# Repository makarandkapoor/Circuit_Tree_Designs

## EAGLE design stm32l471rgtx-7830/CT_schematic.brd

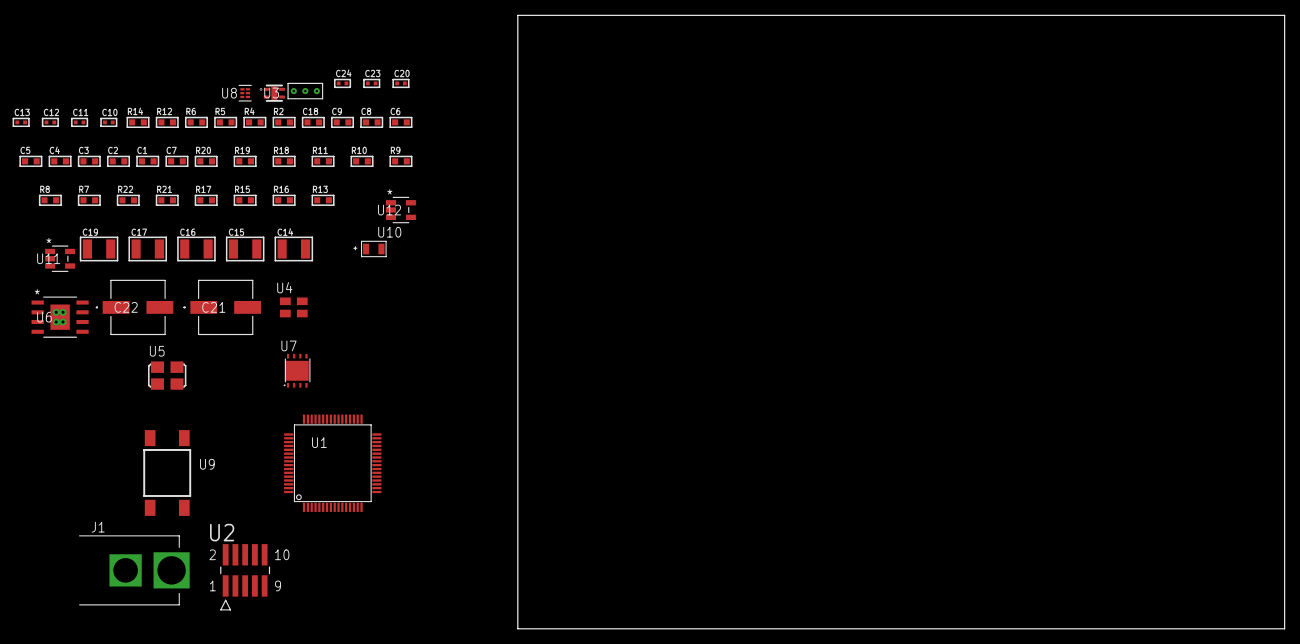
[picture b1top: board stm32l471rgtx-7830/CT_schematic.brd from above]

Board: 2 copper layers, 100.0 x 80.0 mm, 58 parts (0 on the bottom side), 26 nets, no tracks yet.

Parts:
C1, C9, C18: 1e-06; C0603
C2, C3, C4, C5, C6: 1e-07; C0603
C7: 4.7e-06; C0603
C8: 1e-08; C0603
C10, C11, C20: 1e-07; C0402
C12, C13, C23, C24: 1e-08; C0402
C14, C15, C16, C17, C19: 1e-05; C1210
C21, C22: 0.0001; EXV-9H
J1: PJ-037B; PJ-037B_PACKAGE
R2: 1000.0; R0603
R4: 4700.0; R0603
R5, R6, R14: 2200.0; R0603
R7, R8, R9, R10, R11, R18, R19: 10000.0; R0603
R12: 5.0; R0603
R13: 1402.2764227642; R0603
R15, R17: 100000.0; R0603
R16: 153694.38; R0603
R20: 82000.0; R0603
R21: 300000.0; R0603
R22: 120000.0; R0603
U1: STM32L471RGT6; LQFP64
U2: FTSH-105-01-L-DV-K; SAMTEC_FTSH-105-01-L-DV-K
U3: Si7034-A10-IM; SI7034-A10-IM
U4: ASEK-32.768KHz-ECST; ASEK
U5: ASFL1-25MHZ-NCS; ASFL1
U6: MIC5234YME; SOIC-8_EP
U7: LP2951ACSDX/NOPB; WSON-8
U8: TPS3895ADRYR; SON-6
U9: 4-1437565-2; SW_4-1437565-2
U10: Q65110A2395; LGM67K-G1J2-24-Z
U11, U12: nc7sz125m5x; NC7SZ125M5X
U13: Dummy; DUMMY_PACKAGE_127

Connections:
CLK_U1_3: U1.3, U4.3
CLK_U1_5: U1.5, U5.3
GND: C1.2, C2.2, C3.2, C4.2, C5.2, C6.2, C7.2, C8.2, C9.2, C10.2, C11.2, C12.2, C13.2, C14.2, C15.2, C16.2, C17.2, C18.2, C19.2, C20.2, C21.2, C22.2, C23.2, C24.2, J1.2, R2.2, R7.2, R11.2, R12.2, R14.2, R17.2, R20.2, R22.2, U1.12, U1.18, U1.31, U1.47, U1.63, U2.3, U2.5, U3.5, U4.2, U5.2, U6.7, U6.EPAD, U7.3, U7.4, U7.PAD, U8.2, U10.C, U11.2, U11.3, U12.1, U12.3, U13.1
NET_U1_7: R4.1, U1.7, U12.4
NET_U1_58: R5.1, U1.58, U3.2
NET_U1_59: R6.1, U1.59, U3.4
NET_U1_60: R7.1, U1.60
NET_U1_62: U9.3, U9.4
NET_U2_4: R11.1, U2.4
NET_U2_9: R12.1, U2.9
NET_U6_4: R13.2, R14.1, U6.4
NET_U7_5: R15.1, U7.5
NET_U7_7: R16.2, R17.1, U7.7
NET_U8_1: R19.1, R20.1, U8.1
NET_U8_3: R21.2, R22.1, U8.3
NET_U8_4: R18.1, U8.4, U11.4, U12.2
NET_U9_1: R2.1, U9.1, U9.2
PROC_SYS_JTDI: R9.1, U1.50, U2.8
PROC_SYS_JTDO_SWO: U1.55, U2.6
PROC_SYS_JTMS_SWDIO: R10.1, U1.46, U2.2
PROC_TIM1_CH2: U1.42, U13.2
PROC_TIM1_CH4: U1.44, U13.3
RST_OUT_U2_JTAG_RST_B: R8.1, U2.10, U11.1
VCC_S1_5V5: C14.1, C15.1, C18.1, C21.1, C22.1, J1.1, U6.5, U6.8, U7.8
VCC_TIER1_1V8: C1.1, C2.1, C3.1, C4.1, C5.1, C6.1, C7.1, C8.1, C9.1, C10.1, C11.1, C16.1, C17.1, C20.1, C23.1, C24.1, R4.2, R5.2, R6.2, R8.2, R9.2, R10.2, R13.1, R18.2, R19.2, R21.1, U1.1, U1.13, U1.19, U1.32, U1.48, U1.64, U2.1, U3.1, U6.1, U8.6, U11.5, U12.5
VCC_TIER1_3V3: C12.1, C13.1, C19.1, R15.2, R16.1, U4.4, U5.4, U7.1

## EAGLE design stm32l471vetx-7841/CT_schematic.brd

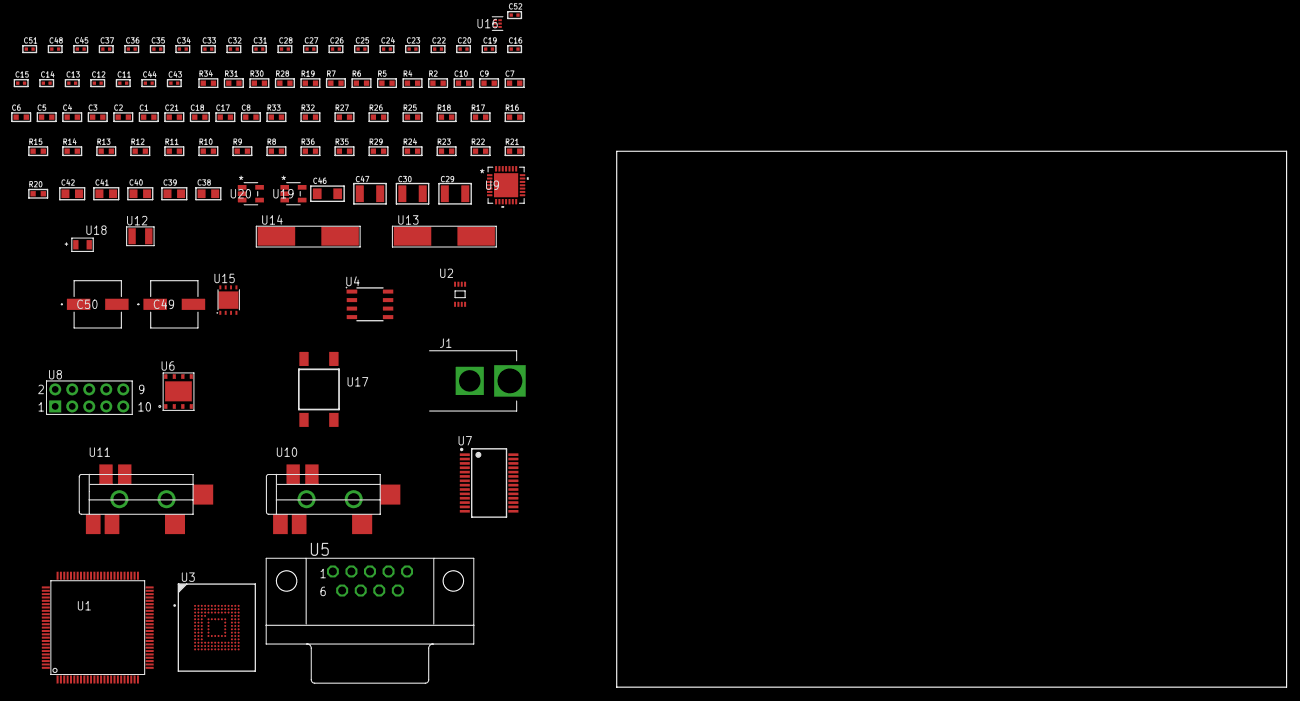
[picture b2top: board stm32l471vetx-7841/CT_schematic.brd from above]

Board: 2 copper layers, 100.0 x 80.0 mm, 107 parts (0 on the bottom side), 67 nets, no tracks yet.

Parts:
C1, C10: 1e-06; C0603
C2, C3, C4, C5, C6, C7: 1e-07; C0603
C8: 4.7e-06; C0603
C9: 1e-08; C0603
C11, C12, C13, C14: 1e-11; C0402
C15, C45, C51, C52: 1e-08; C0402
C16, C19, C20, C22, C23, C24, C25, C26, C27, C28, C33, C34, C35, C36, C37, C48: 1e-07; C0402
C17, C18, C21: 2.2e-06; C0603
C29, C30: 2.2e-05; C1210
C31, C32: 1e-09; C0402
C38, C39, C40, C41, C42: 1e-05; C0805
C43, C44: 2.2e-11; C0402
C46: 1e-05; C1206
C47: 1e-05; C1210
C49, C50: 0.0001; EXV-9H
J1: PJ-037B; PJ-037B_PACKAGE
R2, R31: 1000.0; R0603
R4, R5: 4700.0; R0603
R6, R7: 2200.0; R0603
R8, R32, R33: 10000.0; R0603
R9, R10, R11, R12, R13, R14, R15, R16, R17, R18: 34000.0; R0603
R19: 120.0; R0603
R20, R21, R22, R23, R24, R29: 100000.0; R0603
R25, R26, R27: 47000.0; R0603
R28: 680.0; R0603
R30: 2231.0; R0603
R34: 9100.0; R0603
R35: 680000.0; R0603
R36: 120000.0; R0603
U1: STM32L471VET6; LQFP100
U2: 24AA00T-I/MNY; TDFN-8/6MM
U3: mtfc4gmcdm; TFBGA-153
U4: SN65HVD230D; SOIC-8
U5: 182-009-113R531; 182-009-MALE
U6: SST26VF032B-104I/MF; WFDN-8
U7: ST3241EBPR; SSOP-28
U8: HTSS-105-01-G-D
U9: WM8731CLSEFL; QFN-28
U10, U11: SJ-43515TS-SMT-TR
U12: ABS07-32.768KHZ-7-T
U13: ABLS-25.000MHZ-B2F-T
U14: ABLS-12.288MHZ-B4-T
U15: LP3878SDX-ADJ/NOPB; WSON-8
U16: TPS3895ADRYR; SON-6
U17: 4-1437565-2; SW_4-1437565-2
U18: Q65110A2395; LGM67K-G1J2-24-Z
U19, U20: nc7sz125m5x; NC7SZ125M5X

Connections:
CLK_CRYSTAL_U1_8: C11.1, U1.8, U12.1
CLK_CRYSTAL_U1_9: C12.1, U1.9, U12.2
CLK_CRYSTAL_U1_12: C13.1, U1.12, U13.1
CLK_CRYSTAL_U1_13: C14.1, U1.13, U13.2
CLK_CRYSTAL_U9_1: C43.1, U9.1, U14.1
CLK_CRYSTAL_U9_2: C44.1, U9.2, U14.2
GND: C1.2, C2.2, C3.2, C4.2, C5.2, C6.2, C7.2, C8.2, C9.2, C10.2, C11.2, C12.2, C13.2, C14.2, C15.2, C16.2, C17.2, C18.2, C19.2, C20.2, C21.2, C22.2, C23.2, C24.2, C27.2, C28.2, C32.2, C33.2, C34.2, C35.2, C36.2, C37.2, C38.2, C39.2, C40.2, C41.2, C42.2, C43.2, C44.2, C45.2, C46.2, C47.2, C48.2, C49.2, C50.2, C51.2, C52.2, J1.2, R2.2, R8.2, R20.2, R25.2, R26.2, R27.2, R31.2, R34.2, R36.2, U1.10, U1.19, U1.20, U1.27, U1.49, U1.74, U1.99, U2.4, U3.C4, U3.E7, U3.G5, U3.H10, U3.K8, U3.N2, U3.N5, U3.P4, U3.P6, U4.2, U5.5, U6.4, U6.9, U7.23, U7.25, U8.9, U9.4, U9.15, U9.19, U9.25, U9.26, U9.29, U10.1, U11.1, U15.3, U15.PAD, U16.2, U18.C, U19.1, U19.3, U20.1, U20.3
NET_U1_14: R5.1, U1.14, U20.4
NET_U1_92: R6.1, U1.92, U2.6
NET_U1_93: R7.1, U1.93, U2.5
NET_U1_94: R8.1, U1.94
NET_U1_98: U17.3, U17.4
NET_U3_C2: C18.1, C19.1, U3.C2
NET_U3_K5: R4.1, U3.K5, U19.4
NET_U4_6: R19.2, U4.6
NET_U4_8: R20.1, U4.8
NET_U5_2: R19.2, U4.6, U5.2
NET_U5_3: R19.1, U4.7, U5.3
NET_U7_1: C26.1, U7.1
NET_U7_2: C26.2, U7.2
NET_U7_3: C28.1, U7.3
NET_U7_22: R24.1, U7.22
NET_U7_24: C25.2, U7.24
NET_U7_27: C27.1, U7.27
NET_U7_28: C25.1, U7.28
NET_U8_3: U7.4, U8.3
NET_U8_4: U7.5, U8.4
NET_U8_5: U7.9, U8.5
NET_U8_6: U7.10, U8.6
NET_U9_20: C37.1, C42.1, U9.20
NET_U10_2: C30.1, R26.1, U10.2
NET_U10_5: C29.1, R25.1, U10.5
NET_U11_5: C31.1, C32.1, R27.1, R28.1, U11.5
NET_U15_1: C45.1, U15.1
NET_U15_6: R30.2, R31.1, U15.6
NET_U15_8: R29.1, U15.8
NET_U16_1: R33.1, R34.1, U16.1
NET_U16_3: R35.2, R36.1, U16.3
NET_U16_4: R32.1, U16.4, U19.2, U20.2
NET_U17_1: R2.1, U17.1, U17.2
PROC_CAN1_RX: U1.70, U4.4
PROC_CAN1_TX: U1.71, U4.1
PROC_LPUART1_CTS: U1.52, U7.13
PROC_LPUART1_RTS: U1.51, U7.18
PROC_LPUART1_RX: U1.15, U7.19
PROC_LPUART1_TX: U1.16, U7.14
PROC_QUADSPI_BK1_IO0: U1.36, U6.5
PROC_QUADSPI_BK1_IO1: U1.35, U6.2
PROC_QUADSPI_BK1_IO2: R22.1, U1.32, U6.3
PROC_QUADSPI_BK1_IO3: R23.1, U1.31, U6.7
PROC_QUADSPI_CLK: U1.41, U6.6
PROC_QUADSPI_NCS: R21.1, U1.42, U6.1
PROC_SAI1_FS_A: U1.3, U9.9, U9.11
PROC_SAI1_SCK_A: U1.4, U9.7
PROC_SAI1_SD_A: U1.5, U9.8
PROC_SDMMC1_CK: R18.1, U1.80, U3.M6
PROC_SDMMC1_CMD: R17.1, U1.83, U3.M5
PROC_SDMMC1_D0: R9.1, U1.65, U3.A3
PROC_SDMMC1_D1: R10.1, U1.66, U3.A4
PROC_SDMMC1_D2: R11.1, U1.78, U3.A5
PROC_SDMMC1_D3: R12.1, U1.79, U3.B2
PROC_SDMMC1_D4: R13.1, U1.95, U3.B3
PROC_SDMMC1_D5: R14.1, U1.96, U3.B4
PROC_SDMMC1_D6: R15.1, U1.63, U3.B5
PROC_SDMMC1_D7: R16.1, U1.64, U3.B6
VCC_S1_9V4: C46.1, C49.1, C50.1, J1.1, R29.2, U15.4
VCC_TIER1_3V3: C1.1, C2.1, C3.1, C4.1, C5.1, C6.1, C7.1, C8.1, C9.1, C10.1, C15.1, C16.1, C17.1, C20.1, C21.1, C22.1, C23.1, C24.1, C33.1, C34.1, C35.1, C36.1, C38.1, C39.1, C40.1, C41.1, C47.1, C48.1, C51.1, C52.1, R4.2, R5.2, R6.2, R7.2, R9.2, R10.2, R11.2, R12.2, R13.2, R14.2, R15.2, R16.2, R17.2, R18.2, R21.2, R22.2, R23.2, R24.2, R30.1, R32.2, R33.2, R35.1, U1.6, U1.11, U1.21, U1.22, U1.28, U1.50, U1.73, U1.75, U1.100, U2.8, U3.C6, U3.E6, U3.F5, U3.J10, U3.K9, U3.M4, U3.N4, U3.P3, U3.P5, U4.3, U6.8, U7.26, U9.3, U9.5, U9.12, U9.18, U15.5, U16.6, U19.5, U20.5

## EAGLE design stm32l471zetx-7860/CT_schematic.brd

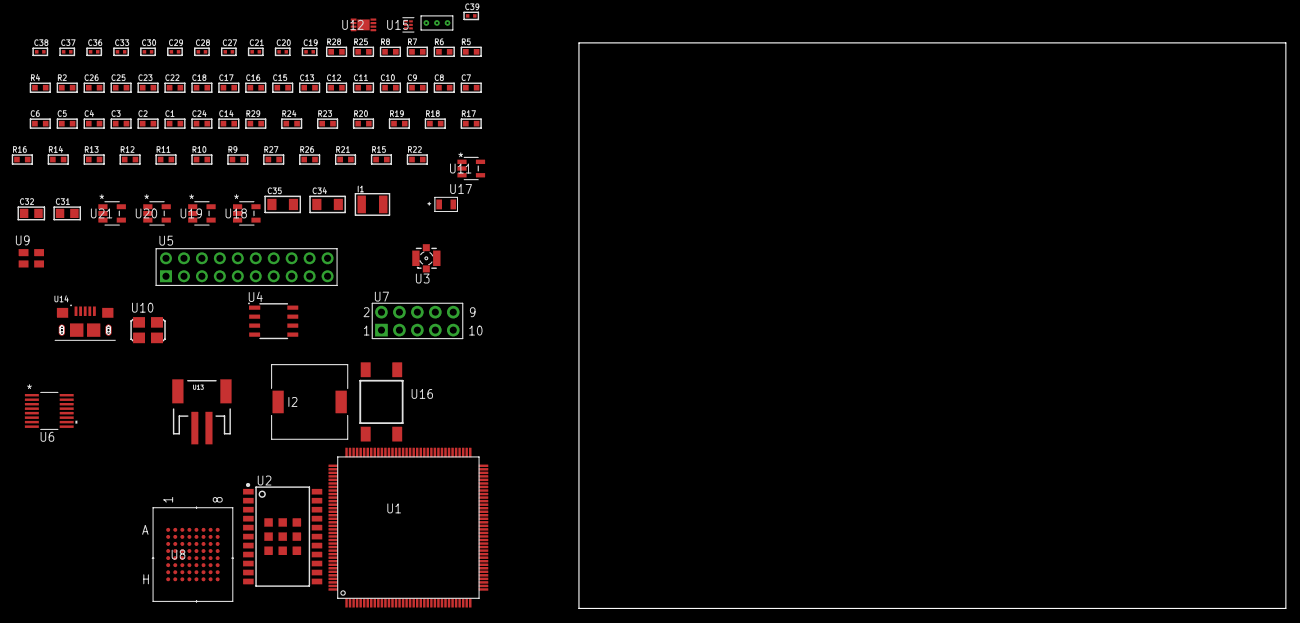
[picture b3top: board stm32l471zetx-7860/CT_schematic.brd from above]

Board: 2 copper layers, 173.4 x 80.0 mm, 90 parts (0 on the bottom side), 97 nets, no tracks yet.

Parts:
C1, C18, C22, C23, C25, C26: 1e-06; C0603
C2, C3, C4, C5, C6, C7, C8, C9, C10, C11, C12, C13, C15, C16: 1e-07; C0603
C14: 4.7e-06; C0603
C17: 1e-08; C0603
C19, C21, C33: 1e-07; C0402
C20, C27, C28, C29, C30, C36, C37, C38, C39: 1e-08; C0402
C24: 2.2e-07; C0603
C31, C32: 1e-05; C0805
C34, C35: 1e-05; C1206
I1: 1e-05; L1210
I2: 2.5e-06; DR1040
R2: 1000.0; R0603
R4, R5, R6: 4700.0; R0603
R7, R8: 2200.0; R0603
R9, R10, R11, R12, R13, R14, R16, R17, R18, R19, R20, R23, R24, R29: 10000.0; R0603
R15: 100000.0; R0603
R21: 220000.0; R0603
R22: 1000000.0; R0603
R25: 9100.0; R0603
R26: 680000.0; R0603
R27: 120000.0; R0603
R28: 2000.0; R0603
U1: STM32L471ZET6; LQFP144
U2: A2200-A
U3: 73412-0114; COAXIAL_C
U4: AT25040B-SSHL-T; SOIC-8
U5: TST-110-05-T-D-RA
U6: LTC2804CGN-1#PBF; SSOP-16
U7: HTSS-105-01-G-D
U8: mt28ew256aba1HPC-0SIT; LBGA-64
U9: ASEK-32.768KHz-ECST; ASEK
U10: ASFL1-25MHZ-NCS; ASFL1
U11: ltc3406es5; TSOT-23-5
U12: MCP73831T-2ACI/MC; DFN8_2X3MC
U13: S2B-PH-SM4-TB(LF)(SN); JST-2-SMD
U14: 10118193-0001LF; FCI_10118193-0001LF
U15: TPS3895ADRYR; SON-6
U16: 4-1437565-2; SW_4-1437565-2
U17: Q65110A2395; LGM67K-G1J2-24-Z
U18, U19, U20, U21: nc7sz125m5x; NC7SZ125M5X
U22: Dummy; DUMMY_PACKAGE_204

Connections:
CLK_U1_8: U1.8, U9.3
CLK_U1_23: U1.23, U10.3
GND: C1.2, C2.2, C3.2, C4.2, C5.2, C6.2, C7.2, C8.2, C9.2, C10.2, C11.2, C12.2, C13.2, C14.2, C15.2, C16.2, C17.2, C18.2, C19.2, C20.2, C21.2, C22.2, C23.2, C25.2, C26.2, C27.2, C28.2, C29.2, C30.2, C31.2, C32.1, C32.2, C33.2, C34.2, C35.2, C36.2, C37.2, C38.2, C39.2, R2.2, R9.2, R21.2, R25.2, R27.2, R28.2, U1.16, U1.30, U1.31, U1.38, U1.51, U1.61, U1.71, U1.83, U1.94, U1.107, U1.120, U1.130, U1.143, U2.7, U2.8, U2.23, U2.24, U2.25, U2.26, U2.27, U2.28, U2.29, U2.30, U2.31, U4.4, U5.4, U5.6, U5.8, U5.10, U5.12, U5.14, U5.16, U5.18, U5.20, U6.8, U7.9, U8.E8, U8.H2, U8.H7, U9.2, U10.2, U11.2, U12.6, U12.9, U13.2, U14.5, U14.6, U14.7, U14.8, U14.9, U15.2, U17.C, U18.2, U18.3, U19.1, U19.3, U20.1, U20.3, U21.1, U21.3, U22.1
INPUT_USBPOWER_5V: C34.1, R29.2, U12.1, U12.2, U14.1
NET_U1_25: R6.1, U1.25, U21.4
NET_U1_128: R8.1, U1.128, U2.16
NET_U1_129: R7.1, U1.129, U2.15
NET_U1_138: R9.1, U1.138
NET_U1_142: U16.3, U16.4
NET_U2_2: R10.2, U2.2
NET_U2_17: R10.1, U2.17
NET_U2_22: R5.1, U2.22, U20.4
NET_U3_1: U2.11, U3.1
NET_U3_2: U2.10, U3.2, U3.3, U3.4
NET_U4_3: R11.1, U4.3
NET_U4_7: R13.1, U4.7
NET_U6_6: C22.1, U6.6
NET_U6_7: C24.1, I1.2, U6.7
NET_U6_9: C23.1, U6.9
NET_U6_10: C24.2, U6.10
NET_U6_11: R15.1, U6.11
NET_U7_3: U6.1, U7.3
NET_U7_4: U6.2, U7.4
NET_U7_5: U6.3, U7.5
NET_U7_6: U6.4, U7.6
NET_U8_B4: R19.1, U8.B4
NET_U8_B5: R4.1, U8.B5, U19.4
NET_U11_3: I2.1, U11.3
NET_U11_5: R21.1, R22.1, U11.5
NET_U11_ATNET_3: I2.2, R22.2
NET_U12_5: R29.1, U12.5
NET_U12_8: R28.1, U12.8
NET_U15_1: R24.1, R25.1, U15.1
NET_U15_3: R26.2, R27.1, U15.3
NET_U15_4: R23.1, U15.4, U18.4, U19.2, U20.2, U21.2
NET_U16_1: R2.1, U16.1, U16.2
PROC_FMC_A0: U1.10, U8.E2
PROC_FMC_A1: U1.11, U8.D2
PROC_FMC_A2: U1.12, U8.C2
PROC_FMC_A3: U1.13, U8.A2
PROC_FMC_A4: U1.14, U8.B2
PROC_FMC_A5: U1.15, U8.D3
PROC_FMC_A6: U1.50, U8.C3
PROC_FMC_A7: U1.53, U8.A3
PROC_FMC_A8: U1.54, U8.B6
PROC_FMC_A9: U1.55, U8.A6
PROC_FMC_A10: U1.56, U8.C6
PROC_FMC_A11: U1.57, U8.D6
PROC_FMC_A12: U1.87, U8.B7
PROC_FMC_A13: U1.88, U8.A7
PROC_FMC_A14: U1.89, U8.C7
PROC_FMC_A15: U1.90, U8.D7
PROC_FMC_A16: U1.80, U8.E7
PROC_FMC_A17: U1.81, U8.B3
PROC_FMC_A18: U1.82, U8.C4
PROC_FMC_A19: U1.2, U8.D5
PROC_FMC_A20: U1.3, U8.D4
PROC_FMC_A21: U1.4, U8.C5
PROC_FMC_A22: U1.5, U8.B8
PROC_FMC_A23: U1.1, U8.C8
PROC_FMC_D0: U1.85, U8.E3
PROC_FMC_D1: U1.86, U8.H3
PROC_FMC_D2: U1.114, U8.E4
PROC_FMC_D3: U1.115, U8.H4
PROC_FMC_D4: U1.58, U8.H5
PROC_FMC_D5: U1.59, U8.E5
PROC_FMC_D6: U1.60, U8.H6
PROC_FMC_D7: U1.63, U8.E6
PROC_FMC_D8: U1.64, U8.F3
PROC_FMC_D9: U1.65, U8.G3
PROC_FMC_D10: U1.66, U8.F4
PROC_FMC_D11: U1.67, U8.G4
PROC_FMC_D12: U1.68, U8.F5
PROC_FMC_D13: U1.77, U8.G6
PROC_FMC_D14: U1.78, U8.F6
PROC_FMC_D15: U1.79, U8.G7
PROC_FMC_NBL0: R20.1, U1.141, U8.F7
PROC_FMC_NE2: R16.1, U1.124, U8.F2
PROC_FMC_NOE: R17.1, U1.118, U8.G2
PROC_FMC_NWAIT: U1.122, U8.A4
PROC_FMC_NWE: R18.1, U1.119, U8.A5
PROC_LPUART1_CTS: U1.74, U6.13
PROC_LPUART1_RTS: U1.73, U6.15
PROC_LPUART1_RX: U1.26, U6.16
PROC_LPUART1_TX: U1.27, U6.14
PROC_PC13: U1.7, U22.2
PROC_PC15_OSC32_OUT: U1.9, U22.3
PROC_SPI1_MISO: U1.42, U4.2
PROC_SPI1_MOSI: U1.43, U4.5
PROC_SPI1_NSS: R12.1, U1.40, U4.1
PROC_SPI1_SCK: U1.41, U4.6
PROC_SYS_JTCK_SWCLK: U1.109, U5.9
PROC_SYS_JTDO_SWO: U1.133, U5.13
PROC_SYS_JTMS_SWDIO: U1.105, U5.7
RST_OUT_U5_SRESET_B: R14.1, U5.15, U18.1
VCC_S1_3V7: C31.1, C35.1, U11.4, U12.3, U12.4, U13.1
VCC_TIER1_3V3: C1.1, C2.1, C3.1, C4.1, C5.1, C6.1, C7.1, C8.1, C9.1, C10.1, C11.1, C12.1, C13.1, C14.1, C15.1, C16.1, C17.1, C18.1, C19.1, C20.1, C21.1, C25.1, C26.1, C27.1, C28.1, C29.1, C30.1, C32.2, C33.1, C36.1, C37.1, C38.1, C39.1, I1.1, I2.2, R4.2, R5.2, R6.2, R7.2, R8.2, R11.2, R12.2, R13.2, R14.2, R15.2, R16.2, R17.2, R18.2, R19.2, R20.2, R22.2, R23.2, R24.2, R26.1, U1.6, U1.17, U1.32, U1.33, U1.39, U1.52, U1.62, U1.72, U1.84, U1.95, U1.106, U1.108, U1.121, U1.131, U1.144, U2.20, U4.8, U5.1, U6.5, U6.12, U8.D8, U8.F1, U8.G5, U9.4, U10.4, U15.6, U18.5, U19.5, U20.5, U21.5

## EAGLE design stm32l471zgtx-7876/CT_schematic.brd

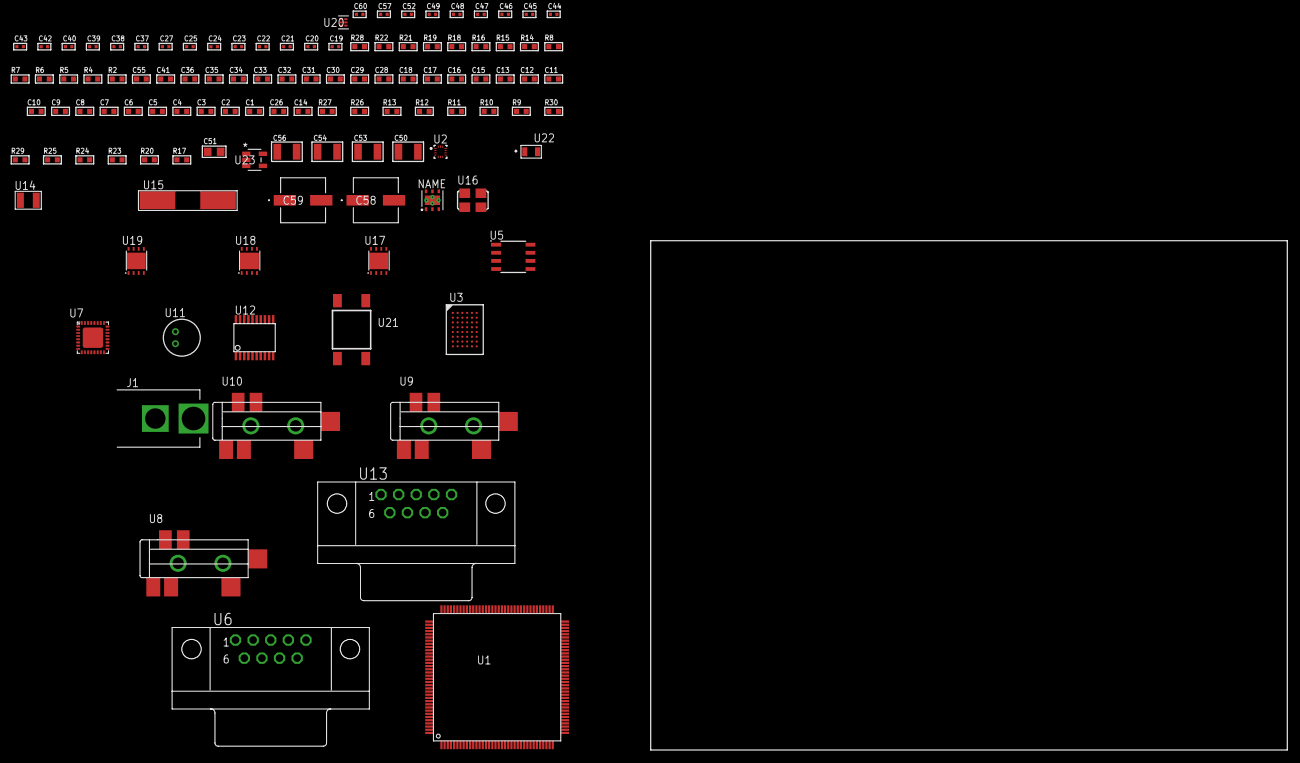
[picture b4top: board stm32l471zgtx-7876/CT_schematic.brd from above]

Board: 2 copper layers, 100.0 x 80.0 mm, 112 parts (0 on the bottom side), 102 nets, no tracks yet.

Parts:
C1, C18, C28, C29, C30, C31, C32, C33, C34, C35, C36, C41: 1e-06; C0603
C2, C3, C4, C5, C6, C7, C8, C9, C10, C11, C12, C13, C15, C16: 1e-07; C0603
C14: 4.7e-06; C0603
C17: 1e-08; C0603
C19, C20, C21, C22: 1e-11; C0402
C23, C24, C25, C37, C38, C39, C40, C42, C43, C44, C45, C46, C47, C57: 1e-07; C0402
C26: 2.2e-06; C0603
C27, C48, C49, C52, C60: 1e-08; C0402
C50, C53, C54, C56: 1e-05; C1210
C51: 1e-05; C0805
C55: 8e-07; R0603
C58, C59: 0.0001; EXV-9H
J1: PJ-037B; PJ-037B_PACKAGE
R2, R19, R22: 1000.0; R0603
R4: 4700.0; R0603
R5, R6, R7, R8: 2200.0; R0603
R9, R10, R11, R12, R13, R26, R27: 10000.0; R0603
R14: 120.0; R0603
R15, R16: 1270.0; R0603
R17, R20, R23, R25: 100000.0; R0603
R18: 200.0; R0603
R21: 2231.0; R0603
R24: 300000.0; R0603
R28: 9100.0; R0603
R29: 680000.0; R0603
R30: 120000.0; R0603
U1: STM32L471ZGT6; LQFP144
U2: BMC150; LGA14R35P5X6_200X200X100
U3: CY62147GE30-45BVXI; VFBGA48
U4: HDC1080DMBR; WSON-6
U5: MCP2562-E/SN; SOIC-8
U6, U13: 182-009-113R531; 182-009-MALE
U7: SGTL5000XNAA3; QFN-32
U8, U9, U10: SJ-43515TS-SMT-TR
U11: WM-64PCT; WM-64PC
U12: SP3203ECY-L/TR; TSSOP20-I
U14: ABS07-32.768KHZ-7-T
U15: ABLS-25.000MHZ-B2F-T
U16: ASFL-24.57MHZ-NCS; ASFL1
U17, U18: LP3878SDX-ADJ/NOPB; WSON-8
U19: LP2951ACSDX/NOPB; WSON-8
U20: TPS3895ADRYR; SON-6
U21: 4-1437565-2; SW_4-1437565-2
U22: Q65110A2395; LGM67K-G1J2-24-Z
U23: nc7sz125m5x; NC7SZ125M5X

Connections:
CLK_CRYSTAL_U1_8: C19.1, U1.8, U14.1
CLK_CRYSTAL_U1_9: C20.1, U1.9, U14.2
CLK_CRYSTAL_U1_23: C21.1, U1.23, U15.1
CLK_CRYSTAL_U1_24: C22.1, U1.24, U15.2
CLK_U7_21: U7.21, U16.3
GND: C1.2, C2.2, C3.2, C4.2, C5.2, C6.2, C7.2, C8.2, C9.2, C10.2, C11.2, C12.2, C13.2, C14.2, C15.2, C16.2, C17.2, C18.2, C19.2, C20.2, C21.2, C22.2, C23.2, C24.2, C25.2, C26.2, C27.2, C28.2, C29.2, C37.2, C38.2, C39.2, C40.2, C41.2, C42.2, C43.2, C46.2, C47.2, C48.2, C49.2, C50.2, C51.2, C52.2, C53.2, C54.2, C55.2, C56.2, C57.2, C58.2, C59.2, C60.2, J1.2, R2.2, R9.2, R16.2, R19.2, R22.2, R25.2, R28.2, R30.2, U1.16, U1.30, U1.31, U1.38, U1.51, U1.61, U1.71, U1.83, U1.94, U1.107, U1.120, U1.130, U1.143, U2.1, U2.6, U2.7, U2.9, U3.D1, U3.E6, U4.2, U4.PAD, U5.2, U5.8, U6.5, U7.1, U7.3, U7.7, U7.EXP, U9.1, U10.1, U11.2, U12.18, U13.5, U16.2, U17.3, U17.PAD, U18.3, U18.PAD, U19.3, U19.4, U19.PAD, U20.2, U22.C, U23.1, U23.3
NET_U1_25: R4.1, U1.25, U23.4
NET_U1_69: R7.1, U1.69, U2.11
NET_U1_70: R8.1, U1.70, U2.14
NET_U1_128: R6.1, U1.128, U4.1
NET_U1_129: R5.1, U1.129, U4.6
NET_U1_138: R9.1, U1.138
NET_U1_142: U21.3, U21.4
NET_U5_6: R14.2, U5.6
NET_U6_2: R14.2, U5.6, U6.2
NET_U6_3: R14.1, U5.7, U6.3
NET_U7_10: C40.1, U7.10
NET_U7_29: R15.1, U7.29
NET_U7_31: R16.1, U7.31
NET_U8_1: U7.4, U8.1
NET_U8_2: U7.2, U8.2
NET_U8_5: U7.6, U8.5
NET_U9_2: C31.1, U9.2
NET_U9_5: C30.1, U9.5
NET_U10_2: C33.1, C34.1, U10.2
NET_U10_5: C32.1, U10.5
NET_U10_13: C33.2, C34.2
NET_U11_1: C35.1, C36.1, C41.1, U7.16, U11.1
NET_U11_15: C35.2, C36.2
NET_U12_1: C44.1, U12.1
NET_U12_2: C46.1, U12.2
NET_U12_3: C44.2, U12.3
NET_U12_4: C45.1, U12.4
NET_U12_5: C45.2, U12.5
NET_U12_6: C47.1, U12.6
NET_U13_2: U12.14, U13.2
NET_U13_3: U12.17, U13.3
NET_U13_7: U12.13, U13.7
NET_U13_8: U12.16, U13.8
NET_U17_1: C49.1, U17.1
NET_U17_6: R18.2, R19.1, U17.6
NET_U17_8: R17.1, U17.8
NET_U18_1: C52.1, U18.1
NET_U18_6: R21.2, R22.1, U18.6
NET_U18_8: R20.1, U18.8
NET_U19_5: R23.1, U19.5
NET_U19_7: R24.2, R25.1, U19.7
NET_U20_1: R27.1, R28.1, U20.1
NET_U20_3: R29.2, R30.1, U20.3
NET_U20_4: R26.1, U20.4, U23.2
NET_U21_1: R2.1, U21.1, U21.2
PROC_CAN1_RX: U1.103, U5.4
PROC_CAN1_TX: U1.104, U5.1
PROC_FMC_A0: U1.10, U3.A3
PROC_FMC_A1: U1.11, U3.A4
PROC_FMC_A2: U1.12, U3.A5
PROC_FMC_A3: U1.13, U3.B3
PROC_FMC_A4: U1.14, U3.B4
PROC_FMC_A5: U1.15, U3.C3
PROC_FMC_A6: U1.50, U3.C4
PROC_FMC_A7: U1.53, U3.D4
PROC_FMC_A8: U1.54, U3.H2
PROC_FMC_A9: U1.55, U3.H3
PROC_FMC_A10: U1.56, U3.H4
PROC_FMC_A11: U1.57, U3.H5
PROC_FMC_A12: U1.87, U3.G3
PROC_FMC_A13: U1.88, U3.G4
PROC_FMC_A14: U1.89, U3.F3
PROC_FMC_A15: U1.90, U3.F4
PROC_FMC_A16: U1.80, U3.E4
PROC_FMC_A17: U1.81, U3.D3
PROC_FMC_D0: U1.85, U3.B6
PROC_FMC_D1: U1.86, U3.C5
PROC_FMC_D2: U1.114, U3.C6
PROC_FMC_D3: U1.115, U3.D5
PROC_FMC_D4: U1.58, U3.E5
PROC_FMC_D5: U1.59, U3.F5
PROC_FMC_D6: U1.60, U3.F6
PROC_FMC_D7: U1.63, U3.G6
PROC_FMC_D8: U1.64, U3.B1
PROC_FMC_D9: U1.65, U3.C1
PROC_FMC_D10: U1.66, U3.C2
PROC_FMC_D11: U1.67, U3.D2
PROC_FMC_D12: U1.68, U3.E2
PROC_FMC_D13: U1.77, U3.F2
PROC_FMC_D14: U1.78, U3.F1
PROC_FMC_D15: U1.79, U3.G1
PROC_FMC_NBL0: U1.141, U3.A1
PROC_FMC_NE2: R12.1, U1.124, U3.B5
PROC_FMC_NOE: R11.1, U1.118, U3.A2
PROC_FMC_NWE: R13.1, U1.119, U3.G5
PROC_LPUART1_CTS: U1.74, U12.8
PROC_LPUART1_RTS: U1.73, U12.10
PROC_LPUART1_RX: U1.26, U12.11
PROC_LPUART1_TX: U1.27, U12.7
PROC_SAI1_FS_A: U1.3, U7.23
PROC_SAI1_SCK_A: U1.4, U7.24
PROC_SAI1_SD_A: U1.5, U7.26
VCC_S1_15V2: C50.1, C53.1, C55.1, C58.1, C59.1, J1.1, R17.2, R20.2, U17.4, U18.4, U19.8
VCC_TIER1_1V2: C37.1, C51.1, R18.1, U7.30, U17.5
VCC_TIER1_3V3: C1.1, C2.1, C3.1, C4.1, C5.1, C6.1, C7.1, C8.1, C9.1, C10.1, C11.1, C12.1, C13.1, C14.1, C15.1, C16.1, C17.1, C18.1, C23.1, C24.1, C25.1, C26.1, C27.1, C29.1, C38.1, C39.1, C42.1, C43.1, C48.1, C54.1, C57.1, C60.1, R4.2, R5.2, R6.2, R7.2, R8.2, R10.1, R10.2, R11.2, R12.2, R13.2, R15.2, R21.1, R26.2, R27.2, R29.1, U1.6, U1.17, U1.32, U1.33, U1.39, U1.52, U1.62, U1.72, U1.84, U1.95, U1.106, U1.108, U1.121, U1.131, U1.144, U2.8, U2.10, U2.12, U2.13, U3.D6, U3.E1, U4.5, U5.5, U7.5, U7.20, U12.12, U12.19, U16.4, U18.5, U20.6, U23.5
VCC_TIER1_5V0: C28.1, C56.1, R23.2, R24.1, U5.3, U19.1

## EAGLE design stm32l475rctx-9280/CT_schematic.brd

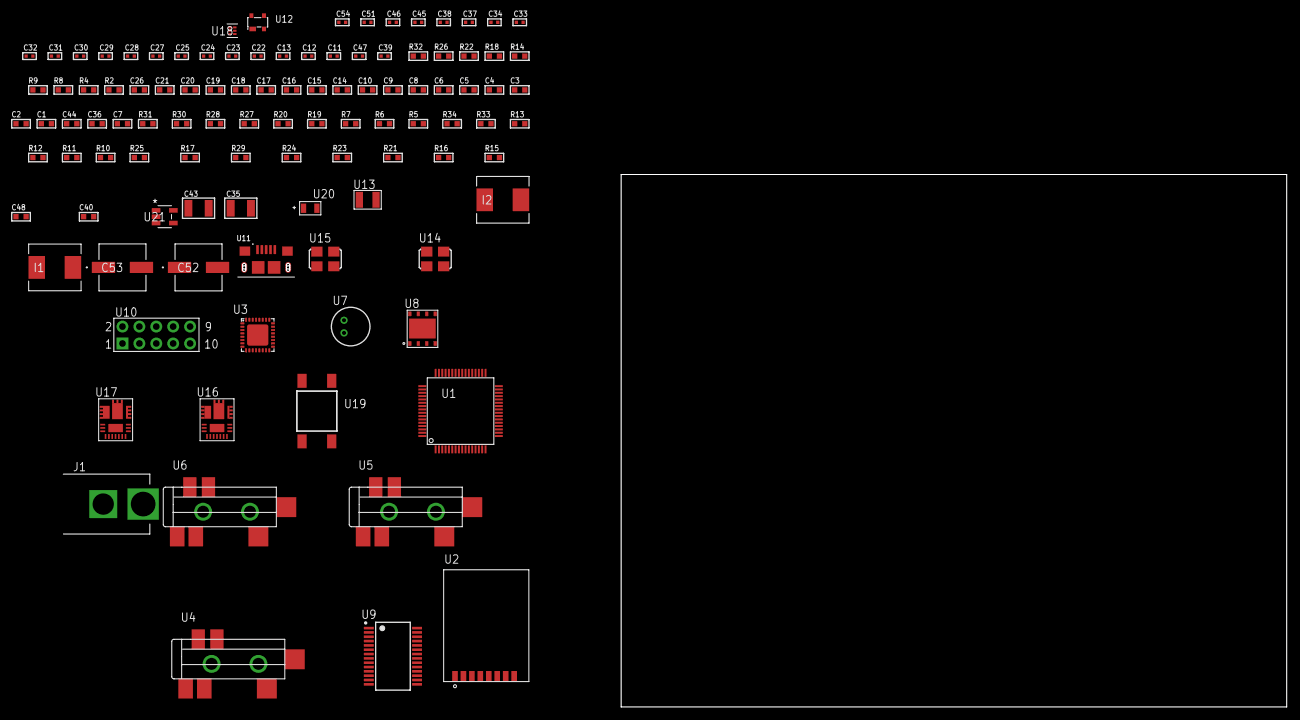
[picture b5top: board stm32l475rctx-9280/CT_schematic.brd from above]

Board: 2 copper layers, 106 parts (0 on the bottom side), 80 nets, no tracks yet.

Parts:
C1, C10, C14, C15, C16, C17, C18, C19, C20, C21, C26: 1e-06; C0603
C2, C3, C4, C5, C6, C8: 1e-07; C0603
C7: 4.7e-06; C0603
C9: 1e-08; C0603
C11, C12: 1e-11; C0402
C13, C22, C23, C24, C25, C27, C28, C29, C30, C31, C32, C37, C38, C45, C46, C51: 1e-07; C0402
C33, C34, C54: 1e-08; C0402
C35, C43: 0.0001; C1210
C36, C44: 2.2e-06; C0603
C39, C47: 8.2e-09; C0402
C40, C48: 2.7406851011734e-07; R0603
C52, C53: 0.0001; EXV-9H
I1, I2: 6.8e-07; IND25X25CZ
J1: PJ-037B; PJ-037B_PACKAGE
R2: 1000.0; R0603
R4: 4700.0; R0603
R5, R6, R7, R30, R31: 10000.0; R0603
R8, R9: 1270.0; R0603
R10, R11, R12, R13: 100000.0; R0603
R14, R22: 0.1; R0603
R15, R23: 4030.2416170974; R0603
R16: 2878.7440122125; R0603
R17, R25: 63.40896969697; R0603
R18, R26: 130.0; R0603
R19, R27: 39000.0; R0603
R20, R28: 49900.0; R0603
R21, R29: 5251.2214765101; R0603
R24: 719.68600305311; R0603
R32: 9100.0; R0603
R33: 680000.0; R0603
R34: 120000.0; R0603
U1: STM32L475RCT7; LQFP64
U2: RFM75-S
U3: SGTL5000XNAA3; QFN-32
U4, U5, U6: SJ-43515TS-SMT-TR
U7: WM-64PCT; WM-64PC
U8: SST26VF064B-104I/MF; WFDN-8
U9: ST3241EBPR; SSOP-28
U10: HTSS-105-01-G-D
U11: 10118193-0001LF; FCI_10118193-0001LF
U12: prtr5v0u2ax; SOT143B
U13: ABS07-32.768KHZ-7-T
U14: ASFL-24.57MHZ-NCS; ASFL1
U15: ASFL1-25MHZ-NCS; ASFL1
U16, U17: IR3899MTR1PBF
U18: TPS3895ADRYR; SON-6
U19: 4-1437565-2; SW_4-1437565-2
U20: Q65110A2395; LGM67K-G1J2-24-Z
U21: nc7sz125m5x; NC7SZ125M5X

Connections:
CLK_CRYSTAL_U1_3: C11.1, U1.3, U13.1
CLK_CRYSTAL_U1_4: C12.1, U1.4, U13.2
CLK_U1_5: U1.5, U15.3
CLK_U3_21: U3.21, U14.3
GND: C1.2, C2.2, C3.2, C4.2, C5.2, C6.2, C7.2, C8.2, C9.2, C10.2, C11.2, C12.2, C13.2, C14.2, C22.2, C23.2, C24.2, C25.2, C26.2, C27.2, C28.2, C31.2, C32.2, C33.2, C34.2, C36.2, C37.2, C38.2, C44.2, C45.2, C46.2, C51.2, C52.2, C53.2, C54.2, J1.2, R2.2, R5.2, R9.2, R14.1, R14.2, R16.2, R19.2, R21.2, R22.1, R22.2, R24.2, R27.2, R29.2, R32.2, R34.2, U1.12, U1.18, U1.31, U1.47, U1.63, U2.1, U3.1, U3.3, U3.7, U3.EXP, U5.1, U6.1, U7.2, U8.4, U8.9, U9.23, U9.25, U10.9, U11.5, U11.6, U11.7, U11.8, U11.9, U12.1, U14.2, U15.2, U16.4, U16.11, U16.17, U17.4, U17.11, U17.17, U18.2, U20.C, U21.1, U21.3
NET_U1_7: R4.1, U1.7, U21.4
NET_U1_60: R5.1, U1.60
NET_U1_62: U19.3, U19.4
NET_U2_3: R6.1, U2.3
NET_U3_10: C25.1, U3.10
NET_U3_29: R8.1, U3.29
NET_U3_31: R9.1, U3.31
NET_U4_1: U3.4, U4.1
NET_U4_2: U3.2, U4.2
NET_U4_5: U3.6, U4.5
NET_U5_2: C16.1, U5.2
NET_U5_5: C15.1, U5.5
NET_U6_2: C18.1, C19.1, U6.2
NET_U6_5: C17.1, U6.5
NET_U6_13: C18.2, C19.2
NET_U7_1: C20.1, C21.1, C26.1, U3.16, U7.1
NET_U7_15: C20.2, C21.2
NET_U9_1: C30.1, U9.1
NET_U9_2: C30.2, U9.2
NET_U9_3: C32.1, U9.3
NET_U9_22: R13.1, U9.22
NET_U9_24: C29.2, U9.24
NET_U9_27: C31.1, U9.27
NET_U9_28: C29.1, U9.28
NET_U10_3: U9.4, U10.3
NET_U10_4: U9.5, U10.4
NET_U10_5: U9.9, U10.5
NET_U10_6: U9.10, U10.6
NET_U16_1: C39.1, R15.1, R16.1, R17.1, R18.1, U16.1, U16.8
NET_U16_2: C38.1, U16.2
NET_U16_3: C39.2, C40.1, C40.2, U16.3
NET_U16_5: R19.1, U16.5
NET_U16_10: C36.1, U16.10
NET_U16_12: C35.1, I1.1, U16.12
NET_U16_14: C35.2, U16.14
NET_U16_15: R20.1, R21.1, U16.15
NET_U16_ATNET_3: I1.2, R15.2
NET_U16_ATNET_4: C40.2, R17.2
NET_U17_1: C47.1, R23.1, R24.1, R25.1, R26.1, U17.1, U17.8
NET_U17_2: C46.1, U17.2
NET_U17_3: C47.2, C48.1, C48.2, U17.3
NET_U17_5: R27.1, U17.5
NET_U17_10: C44.1, U17.10
NET_U17_12: C43.1, I2.1, U17.12
NET_U17_14: C43.2, U17.14
NET_U17_15: R28.1, R29.1, U17.15
NET_U17_ATNET_3: I2.2, R23.2
NET_U17_ATNET_4: C48.2, R25.2
NET_U18_1: R31.1, R32.1, U18.1
NET_U18_3: R33.2, R34.1, U18.3
NET_U18_4: R30.1, U18.4, U21.2
NET_U19_1: R2.1, U19.1, U19.2
PROC_LPUART1_CTS: U1.34, U9.13
PROC_LPUART1_RTS: U1.33, U9.18
PROC_LPUART1_RX: U1.8, U9.19
PROC_LPUART1_TX: U1.9, U9.14
PROC_QUADSPI_BK1_IO0: U1.27, U8.5
PROC_QUADSPI_BK1_IO1: U1.26, U8.2
PROC_QUADSPI_BK1_IO2: R11.1, U1.23, U8.3
PROC_QUADSPI_BK1_IO3: R12.1, U1.22, U8.7
PROC_QUADSPI_CLK: U1.29, U8.6
PROC_QUADSPI_NCS: R10.1, U1.30, U8.1
PROC_SAI1_FS_B: U1.20, U3.23
PROC_SAI1_SCK_B: U1.55, U3.24
PROC_SAI1_SD_B: U1.57, U3.25
PROC_SPI3_MISO: U1.52, U2.7
PROC_SPI3_MOSI: U1.53, U2.6
PROC_SPI3_NSS: R7.1, U1.50, U2.4
PROC_SPI3_SCK: U1.51, U2.5
PROC_USB_OTG_FS_DM: U1.44, U11.2, U12.3
PROC_USB_OTG_FS_DP: U1.45, U11.3, U12.2
PROC_USB_OTG_FS_VBUS: U1.42, U11.1, U12.4
VCC_S1_16V5: C37.1, C45.1, C52.1, C53.1, J1.1, R20.2, R28.2, U16.9, U17.9
VCC_TIER1_1V2: C22.1, I1.2, R15.2, U3.30
VCC_TIER1_3V3: C1.1, C2.1, C3.1, C4.1, C5.1, C6.1, C7.1, C8.1, C9.1, C10.1, C13.1, C14.1, C23.1, C24.1, C27.1, C28.1, C33.1, C34.1, C51.1, C54.1, I2.2, R4.2, R6.2, R7.2, R8.2, R10.2, R11.2, R12.2, R13.2, R23.2, R30.2, R31.2, R33.1, U1.1, U1.13, U1.19, U1.32, U1.48, U1.64, U2.2, U3.5, U3.20, U8.8, U9.26, U14.4, U15.4, U18.6, U21.5

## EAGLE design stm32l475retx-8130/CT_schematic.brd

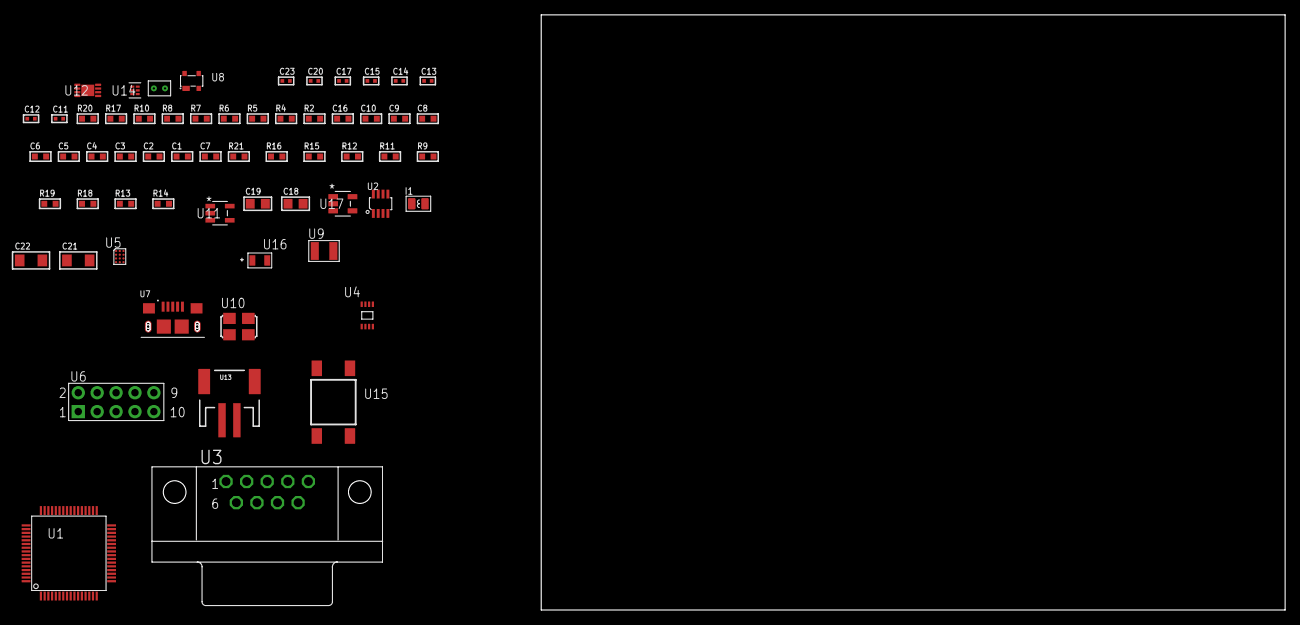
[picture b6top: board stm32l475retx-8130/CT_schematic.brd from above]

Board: 2 copper layers, 61 parts (0 on the bottom side), 37 nets, no tracks yet.

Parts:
C1, C10, C16: 1e-06; C0603
C2, C3, C4, C5, C6, C8: 1e-07; C0603
C7: 4.7e-06; C0603
C9: 1e-08; C0603
C11, C12: 1e-11; C0402
C13, C15, C20: 1e-07; C0402
C14, C17, C23: 1e-08; C0402
C18, C19: 1e-05; C0805
C21, C22: 1e-05; C1206
I1: 3.3e-06; L0806
R2: 1000.0; R0603
R4: 4700.0; R0603
R5, R6, R7, R8: 2200.0; R0603
R9, R11, R12, R15, R16, R21: 10000.0; R0603
R10: 120.0; R0603
R13: 220000.0; R0603
R14: 1000000.0; R0603
R17: 9100.0; R0603
R18: 680000.0; R0603
R19: 120000.0; R0603
R20: 2000.0; R0603
U1: STM32L475RET6; LQFP64
U2: MAX3051EKA+T; SOT-23-8
U3: 182-009-113R531; 182-009-MALE
U4: 24AA02T-I/MNY; TDFN-8/6MM
U5: TSC2014IYZGT
U6: HTSS-105-01-G-D
U7: 10118193-0001LF; FCI_10118193-0001LF
U8: prtr5v0u2ax; SOT143B
U9: ABS07-32.768KHZ-7-T
U10: ASFL1-25MHZ-NCS; ASFL1
U11: ltc3406es5; TSOT-23-5
U12: MCP73831T-2ACI/MC; DFN8_2X3MC
U13: S2B-PH-SM4-TB(LF)(SN); JST-2-SMD
U14: TPS3895ADRYR; SON-6
U15: 4-1437565-2; SW_4-1437565-2
U16: Q65110A2395; LGM67K-G1J2-24-Z
U17: nc7sz125m5x; NC7SZ125M5X
U18: Dummy; DUMMY_PACKAGE_138

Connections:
CLK_CRYSTAL_U1_3: C11.1, U1.3, U9.1
CLK_CRYSTAL_U1_4: C12.1, U1.4, U9.2
CLK_U1_5: U1.5, U10.3
GND: C1.2, C2.2, C3.2, C4.2, C5.2, C6.2, C7.2, C8.2, C9.2, C10.2, C11.2, C12.2, C13.2, C14.2, C15.2, C16.2, C17.2, C18.2, C19.1, C19.2, C20.2, C21.2, C22.2, C23.2, R2.2, R9.2, R13.2, R17.2, R19.2, R20.2, U1.12, U1.18, U1.31, U1.47, U1.63, U2.2, U2.8, U3.5, U4.4, U4.7, U5.B2, U5.D2, U6.9, U7.5, U7.6, U7.7, U7.8, U7.9, U8.1, U10.2, U11.2, U12.6, U12.9, U13.2, U14.2, U16.C, U17.1, U17.3, U18.1
INPUT_USBPOWER_5V: C21.1, R21.2, U1.42, U7.1, U8.4, U12.1, U12.2
NET_U1_7: R4.1, U1.7, U17.4
NET_U1_29: R7.1, U1.29, U4.6
NET_U1_30: R8.1, U1.30, U4.5
NET_U1_57: U15.3, U15.4
NET_U1_58: R5.1, U1.58, U5.D1
NET_U1_59: R6.1, U1.59, U5.C1
NET_U1_60: R9.1, U1.60
NET_U2_6: R10.2, U2.6
NET_U3_2: R10.2, U2.6, U3.2
NET_U3_3: R10.1, U2.7, U3.3
NET_U5_B1: R12.1, U5.B1
NET_U5_C2: R11.1, U5.C2
NET_U6_3: U5.B3, U6.3
NET_U6_4: U5.D3, U6.4
NET_U6_5: U5.A3, U6.5
NET_U6_6: U5.C3, U6.6
NET_U11_3: I1.1, U11.3
NET_U11_5: R13.1, R14.1, U11.5
NET_U11_ATNET_3: I1.2, R14.2
NET_U12_5: R21.1, U12.5
NET_U12_8: R20.1, U12.8
NET_U14_1: R16.1, R17.1, U14.1
NET_U14_3: R18.2, R19.1, U14.3
NET_U14_4: R15.1, U14.4, U17.2
NET_U15_1: R2.1, U15.1, U15.2
PROC_CAN1_RX: U1.61, U2.4
PROC_CAN1_TX: U1.62, U2.1
PROC_DAC1_OUT2: U1.21, U18.2
PROC_USB_OTG_FS_DM: U1.44, U7.2, U8.3
PROC_USB_OTG_FS_DP: U1.45, U7.3, U8.2
VCC_S1_3V7: C18.1, C22.1, U11.4, U12.3, U12.4, U13.1
VCC_TIER1_3V3: C1.1, C2.1, C3.1, C4.1, C5.1, C6.1, C7.1, C8.1, C9.1, C10.1, C13.1, C14.1, C15.1, C16.1, C17.1, C19.2, C20.1, C23.1, I1.2, R4.2, R5.2, R6.2, R7.2, R8.2, R11.2, R12.2, R14.2, R15.2, R16.2, R18.1, U1.1, U1.13, U1.19, U1.32, U1.48, U1.64, U2.3, U4.8, U5.A2, U10.4, U14.6, U17.5
